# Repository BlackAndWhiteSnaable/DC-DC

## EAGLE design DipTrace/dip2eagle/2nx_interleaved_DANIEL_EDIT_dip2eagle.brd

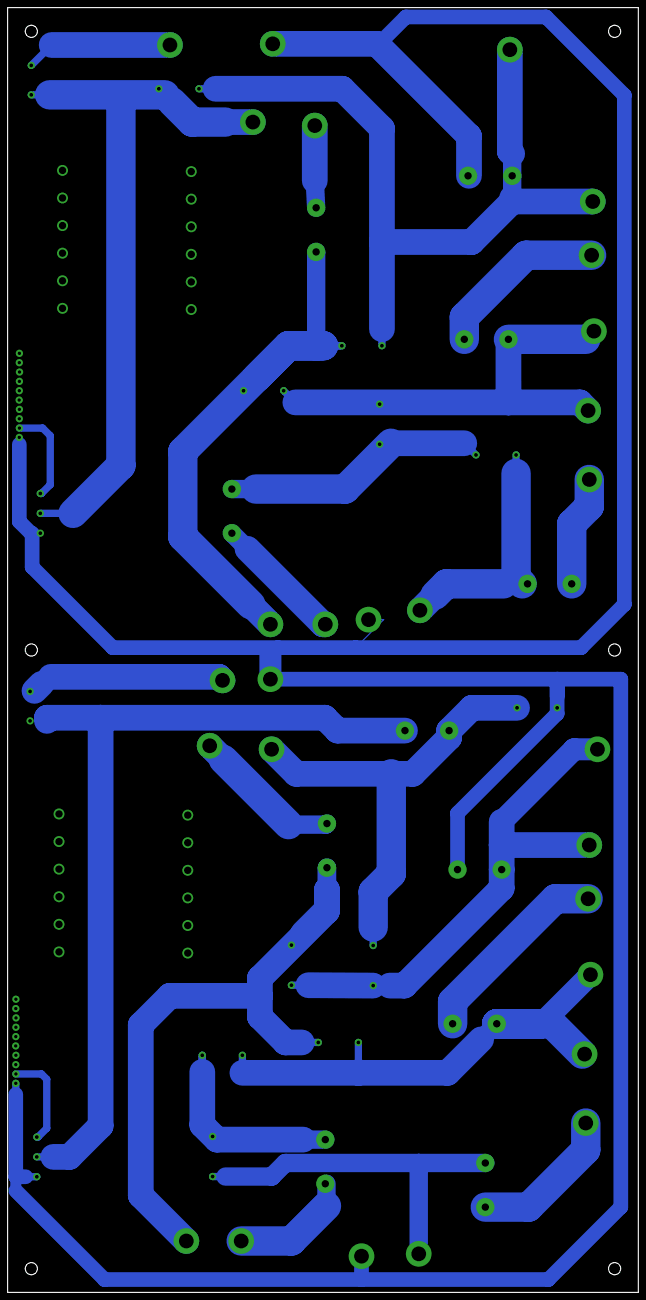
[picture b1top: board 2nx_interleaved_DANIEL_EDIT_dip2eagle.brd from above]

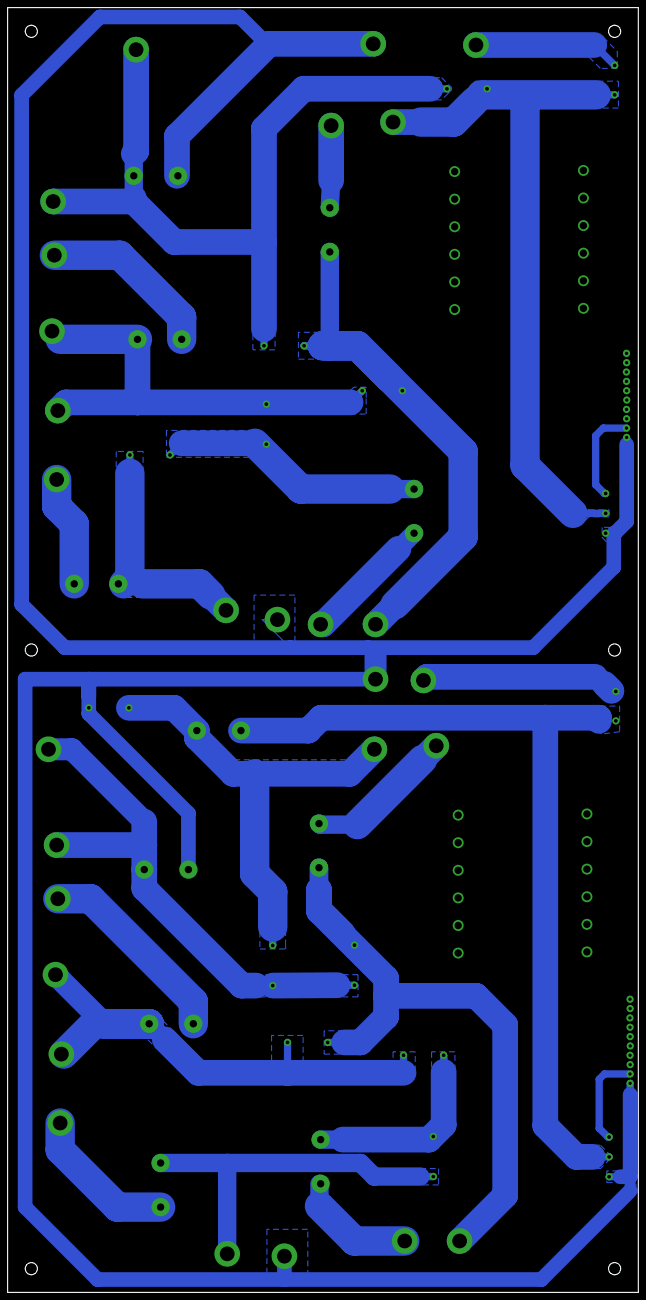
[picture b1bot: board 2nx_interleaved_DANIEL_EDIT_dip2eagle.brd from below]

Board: 2 copper layers, 171.4 x 349.2 mm, 120 parts (94 on the bottom side), 18 nets.

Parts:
PAD1, PAD46, PAD47, PAD48, PAD49, PAD50, PAD52, PAD53, PAD54, PAD55, PAD56, PAD57, PAD58, PAD67, PAD69, PAD70, PAD93, PAD94, PAD95, PAD96, PAD97, PAD98, PAD99, PAD100, PAD101, PAD102, PAD103, PAD104: PAD
PAD2, PAD3, PAD5, PAD7, PAD9, PAD11, PAD13, PAD15, PAD18, PAD20, PAD22, PAD24, PAD26, PAD28, PAD30, PAD32, PAD34, PAD36, PAD38, PAD40, PAD42, PAD44: PAD1
PAD4, PAD6, PAD8, PAD10, PAD12, PAD14, PAD16, PAD17, PAD19, PAD21, PAD23, PAD25, PAD71, PAD72, PAD73, PAD74, PAD75, PAD76, PAD77, PAD78, PAD79, PAD80, PAD81, PAD82: PAD_PAD2
PAD27, PAD29, PAD31, PAD33, PAD35, PAD37, PAD39, PAD41, PAD43, PAD45, PAD83, PAD84, PAD85, PAD86, PAD87, PAD88, PAD89, PAD90, PAD91, PAD92, PAD115, PAD116: PAD_PAD14
PAD51, PAD59, PAD60, PAD61, PAD62, PAD63, PAD64, PAD65, PAD66, PAD68, PAD105, PAD106, PAD107, PAD108, PAD109, PAD110, PAD111, PAD112, PAD113, PAD114: PAD_PAD29
U1: P116
U2: P117
U3: P118
U4: P119

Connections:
NET_2: PAD2.1, PAD9.1, PAD14.1, PAD32.1
NET_3: PAD1.1, PAD22.1, PAD24.1, PAD25.1, U3.1
NET_5: PAD3.1, PAD5.1, PAD10.1, PAD20.1, PAD28.1, PAD30.1, PAD36.1, U1.1, U3.1_1
NET_6: PAD62.1, PAD81.1
NET_8: PAD17.1, PAD33.1
NET_9: PAD4.1, PAD6.1, PAD7.1, PAD13.1, PAD16.1, PAD21.1, PAD26.1, PAD45.1, PAD94.1, U2.1
NET_10: PAD19.1, PAD31.1
NET_11: PAD15.1, PAD35.1
NET_12: PAD1.1, PAD21.1, PAD23.1, PAD27.1, PAD29.1, PAD46.1, PAD48.1, PAD70.1, PAD82.1, PAD91.1, U1.1_1, U2.1_1
NET_13: PAD16.1, PAD47.1
NET_15: PAD8.1, PAD12.1, PAD15.1, PAD17.1, PAD18.1, PAD19.1, PAD34.1, PAD61.1, PAD63.1, PAD77.1
NET_16: PAD14.1, PAD69.1, PAD71.1, PAD72.1, U4.1
NET_20: PAD18.1, PAD65.1, PAD79.1
NET_21: PAD64.1, PAD78.1
NET_22: PAD68.1, PAD73.1
NET_23: PAD66.1, PAD76.1
NET_24: PAD11.1, PAD20.1, PAD22.1, PAD67.1, PAD74.1, PAD75.1, PAD80.1, PAD93.1, U4.1_1
NET_25: PAD92.1, U2.1_1

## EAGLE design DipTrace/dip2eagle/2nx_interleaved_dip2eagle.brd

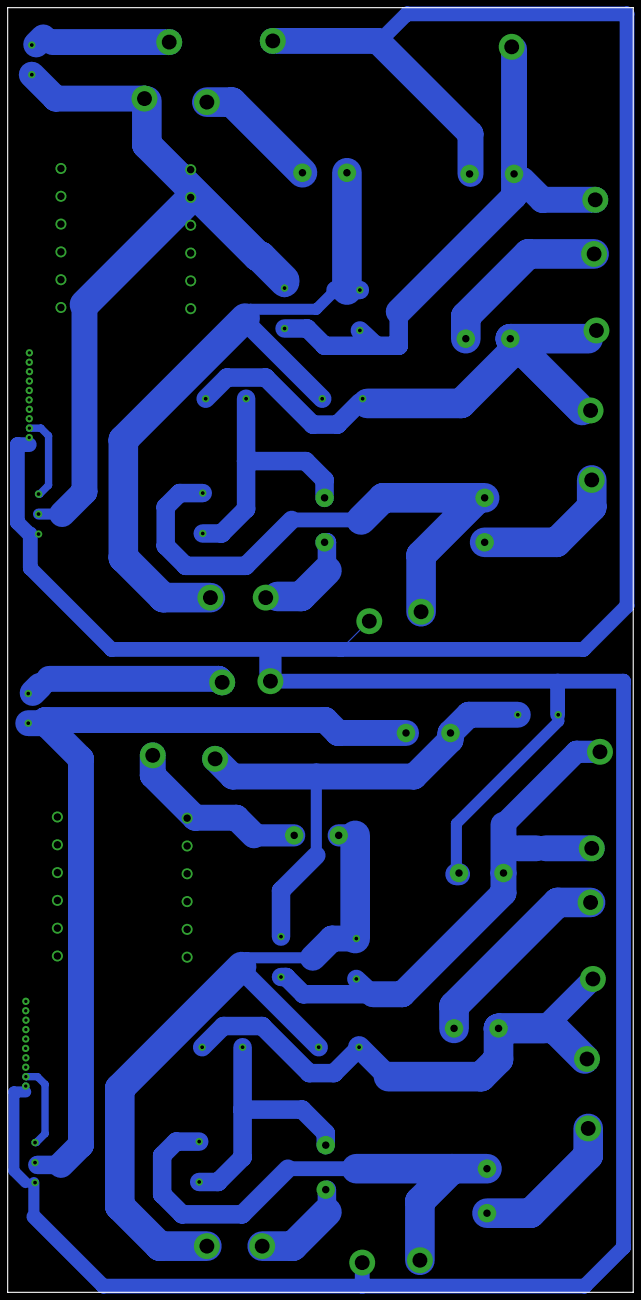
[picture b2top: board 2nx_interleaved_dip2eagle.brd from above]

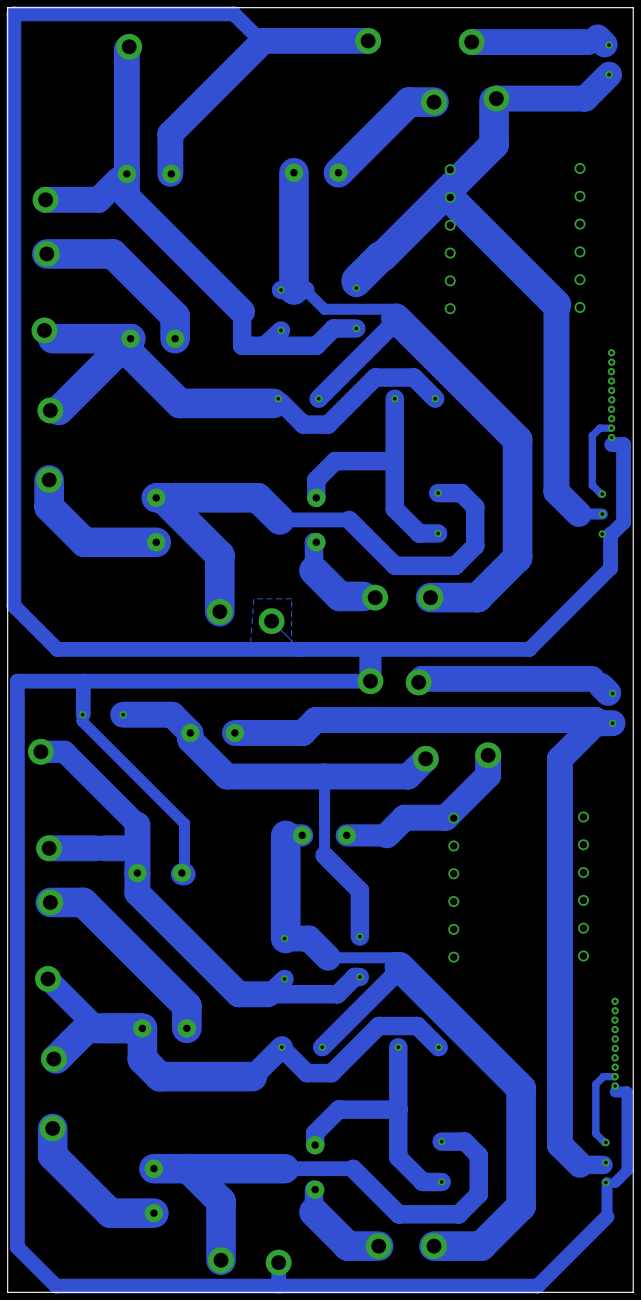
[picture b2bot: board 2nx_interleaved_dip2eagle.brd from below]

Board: 2 copper layers, 168.8 x 346.6 mm, 120 parts (94 on the bottom side), 25 nets.

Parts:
PAD1, PAD2, PAD3, PAD4, PAD5, PAD6, PAD7, PAD8, PAD9, PAD10, PAD11, PAD12, PAD13, PAD14, PAD15, PAD16, PAD17, PAD18, PAD19, PAD20, PAD21, PAD22: PAD1
Pad1, Pad24, Pad25, Pad26, Pad27, Pad28, Pad30, Pad31, Pad32, Pad33, Pad34, Pad35, Pad36, Pad45, Pad47, Pad48, Pad71, Pad72, Pad73, Pad74, Pad75, Pad76, Pad77, Pad78, Pad79, Pad80, Pad81, Pad82: Pad
Pad2, Pad3, Pad4, Pad5, Pad6, Pad7, Pad8, Pad9, Pad10, Pad11, Pad12, Pad13, Pad49, Pad50, Pad51, Pad52, Pad53, Pad54, Pad55, Pad56, Pad57, Pad58, Pad59, Pad60: Pad_Pad2
Pad14, Pad15, Pad16, Pad17, Pad18, Pad19, Pad20, Pad21, Pad22, Pad23, Pad61, Pad62, Pad63, Pad64, Pad65, Pad66, Pad67, Pad68, Pad69, Pad70, Pad93, Pad94: Pad_Pad14
Pad29, Pad37, Pad38, Pad39, Pad40, Pad41, Pad42, Pad43, Pad44, Pad46, Pad83, Pad84, Pad85, Pad86, Pad87, Pad88, Pad89, Pad90, Pad91, Pad92: Pad_Pad29
U1: P116
U2: P117
U3: P118
U4: P119

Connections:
Net_0: PAD4.1, Pad45.1
Net_1: PAD3.1, Pad36.1, U1.1, U3.1_1
Net_2: PAD2.1, PAD9.1, Pad14.1, Pad32.1
Net_3: PAD1.1, Pad22.1, Pad24.1, Pad25.1, U3.1
Net_4: PAD21.1, Pad1.1, Pad23.1, Pad27.1, Pad29.1, Pad48.1, Pad70.1, Pad82.1, Pad91.1, U1.1_1, U2.1_1
Net_5: PAD5.1, PAD10.1, Pad20.1, Pad28.1, Pad30.1
Net_6: PAD6.1, PAD7.1, Pad16.1
Net_7: PAD8.1, Pad18.1, Pad34.1
Net_9: Pad21.1, Pad26.1
Net_10: Pad19.1, Pad31.1
Net_11: Pad15.1, Pad35.1
Net_12: Pad46.1, U1.1_1
Net_13: PAD16.1, Pad47.1
Net_14: PAD13.1, Pad94.1, U2.1
Net_15: PAD15.1, PAD19.1, Pad61.1, Pad77.1
Net_16: PAD14.1, Pad69.1, Pad71.1, Pad72.1, U4.1
Net_18: PAD11.1, PAD20.1, Pad67.1, Pad74.1, Pad75.1
Net_19: PAD12.1, PAD17.1, Pad63.1
Net_20: PAD18.1, Pad65.1, Pad79.1
Net_21: Pad64.1, Pad78.1
Net_22: Pad68.1, Pad73.1
Net_23: Pad66.1, Pad76.1
Net_24: PAD22.1, Pad80.1, Pad93.1, U4.1_1
Net_25: Pad92.1, U2.1_1
Net_26: Pad62.1, Pad81.1
